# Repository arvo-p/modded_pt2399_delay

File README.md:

Based on TweakTone's delay pedal, this PCB design is one sided.

## Schema

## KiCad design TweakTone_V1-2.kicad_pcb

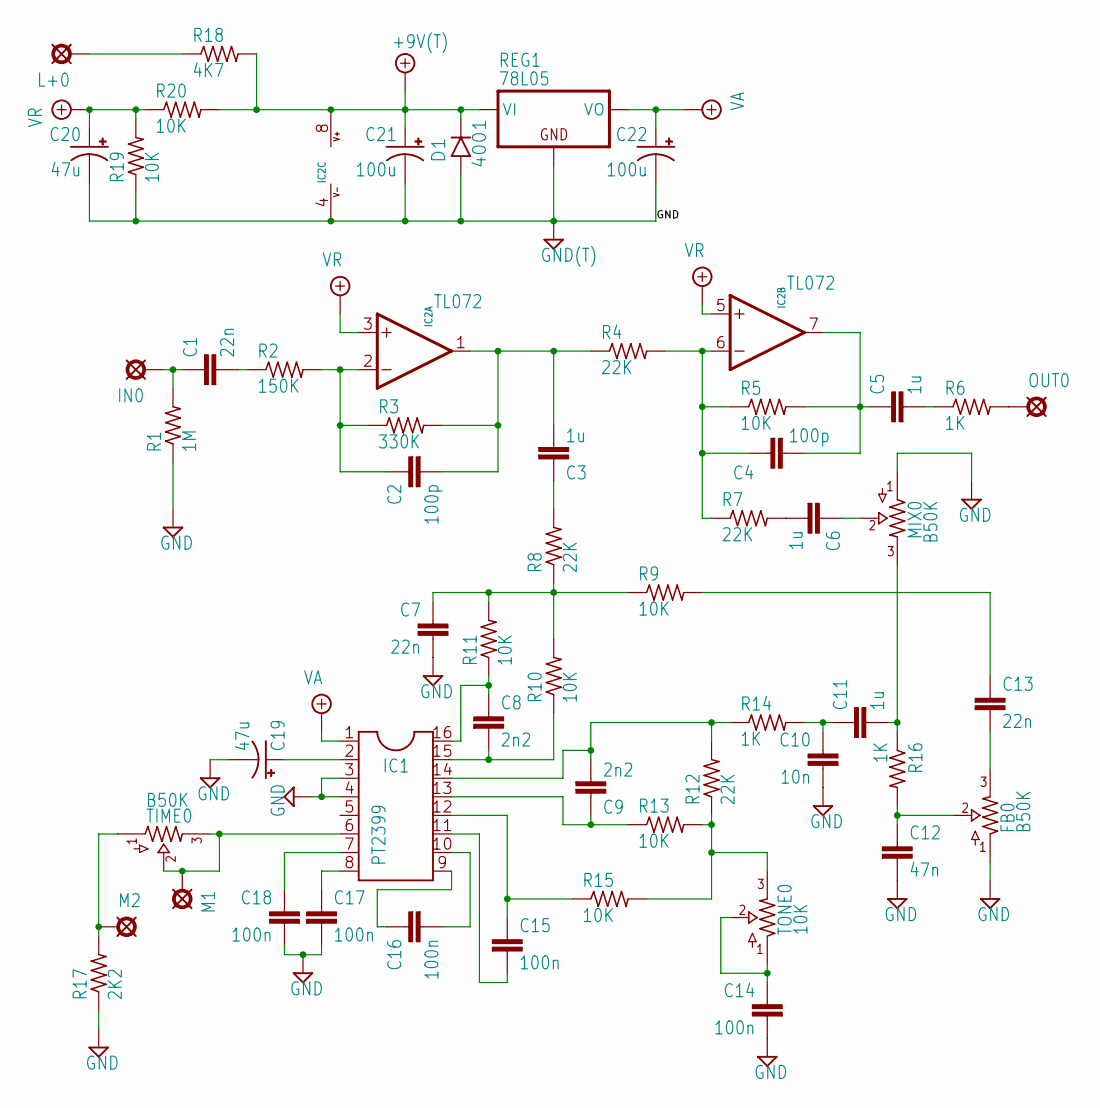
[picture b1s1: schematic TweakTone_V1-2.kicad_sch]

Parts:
C1, C7, C13: 22n; 072X025
C2, C4: 100p; 050X030_025
C3, C5, C6, C11: 1u; 072X045
C8, C9: 2n2; 072X025
C10: 10n; 072X025
C12: 47n; 072X025
C14: 100n; 072X025
C15, C16, C17, C18: 100n; SMALL-5MM
C19, C20: 47u; 050_020_1
C21, C22: 100u; 050_020_1
D1: 4001; DO41-3
FB0: B50K; 16MM
IC1: PT2399; DIL16
IC2: TL072; DIL08
IN0: IN; SQUARE
L+0: IN; SQUARE
M1, M2: PAD8; OCTOGON
MIX0: B50K; 16MM
OUT0: out; SQUARE
R1: 1M; R0207_3
R2: 150K; R0207_3
R3: 330K; R0207_3
R4, R7, R8, R12: 22K; R0207_3
R5, R9, R10, R11, R13, R15, R19, R20: 10K; R0207_3
R6, R14, R16: 1K; R0207_3
R17: 2K2; R0207_3
R18: 4K7; R0207_3
REG1: 78L05; TO92-
TIME0: B50K; 16MM
TONE0: 10K; 2262_TRIM

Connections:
+9V(T): C21.+, D1.C, IC2.8 (V+), R18.2, R20.2, REG1.1 (VI); also elsewhere on the board
GND: C7.2, C10.2, C12.2, C14.2, C17.2, C18.2, C19.-, C20.-, C21.-, C22.-, D1.A, FB0.1, IC1.3, IC1.4, IC2.4 (V-), MIX0.1, R1.1, R17.1, R19.1, REG1.2 (GND); also elsewhere on the board
unnamed: C1.2, R2.1
unnamed: C3.1, R8.2
unnamed: C5.2, R6.1
unnamed: C6.1, MIX0.2
unnamed: C6.2, R7.2
unnamed: C7.1, R8.1, R9.1, R10.2, R11.2
unnamed: C8.1, IC1.16, R11.1
unnamed: C8.2, IC1.15, R10.1
unnamed: C9.1, IC1.13, R13.1
unnamed: C9.2, IC1.14, R12.2, R14.1
unnamed: C10.1, C11.1, R14.2
unnamed: C11.2, MIX0.3, R16.1
unnamed: C12.1, FB0.2, R16.2
unnamed: C13.1, R9.2
unnamed: C13.2, FB0.3
unnamed: C14.1, TONE0.1, TONE0.2
unnamed: C15.1, IC1.12, R15.1
unnamed: C15.2, IC1.11
unnamed: C16.1, IC1.9
unnamed: C16.2, IC1.10
unnamed: C17.1, IC1.8
unnamed: C18.1, IC1.7
unnamed: C19.+, IC1.2
unnamed: C2.1, IC2.2 (-IN), R2.2, R3.1
unnamed: C2.2, C3.2, IC2.1 (OUT), R3.2, R4.1
unnamed: C4.1, IC2.6 (-IN), R4.2, R5.1, R7.1
unnamed: C4.2, C5.1, IC2.7 (OUT), R5.2
unnamed: C1.1, IN0.1 (PAD), R1.2
unnamed: L+0.1 (PAD), R18.1
unnamed: IC1.6, M1.1 (PAD), TIME0.2, TIME0.3
unnamed: M2.1 (PAD), R17.2, TIME0.1
unnamed: OUT0.1 (PAD), R6.2
unnamed: R12.1, R13.2, R15.2, TONE0.3
VA: C22.+, IC1.1, REG1.3 (VO)
VR: C20.+, IC2.3 (+IN), IC2.5 (+IN), R19.2, R20.1

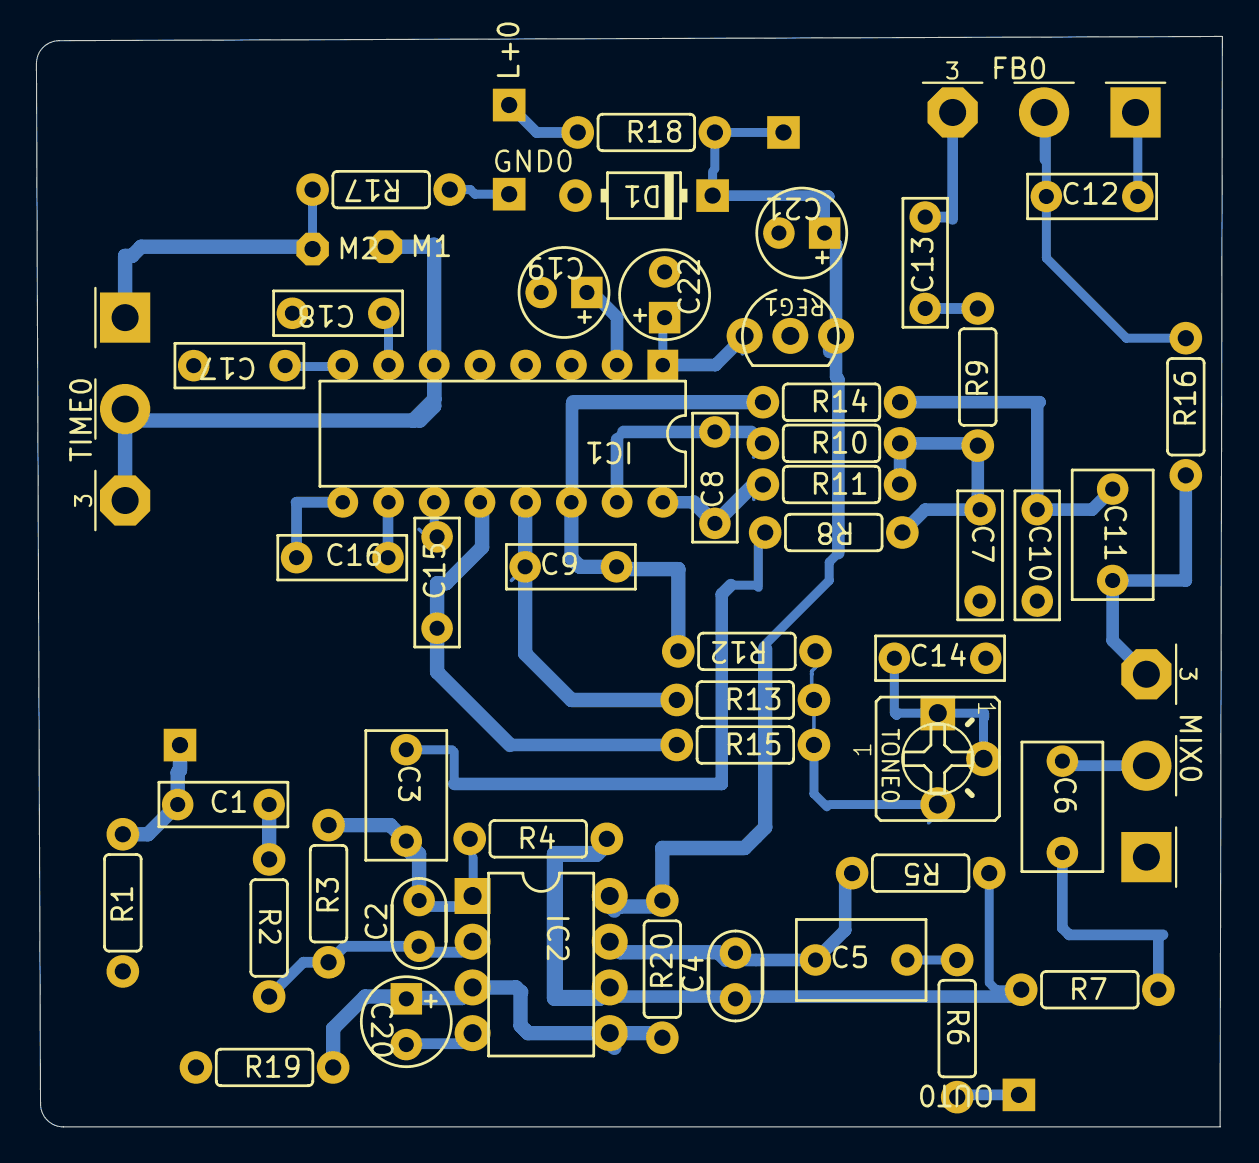
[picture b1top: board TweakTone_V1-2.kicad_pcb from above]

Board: 2 copper layers, 65.9 x 60.6 mm, 57 parts (0 on the bottom side), 37 nets.

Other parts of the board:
+9V0: +9V(T); SQUARE
GND0: GND(T); SQUARE

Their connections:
+9V(T): +9V0.1; also elsewhere on the board
GND: GND0.1; also elsewhere on the board

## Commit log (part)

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2026-02-22 22 February
2026-06-20 fix missing connection between MIX0 and wet signal
